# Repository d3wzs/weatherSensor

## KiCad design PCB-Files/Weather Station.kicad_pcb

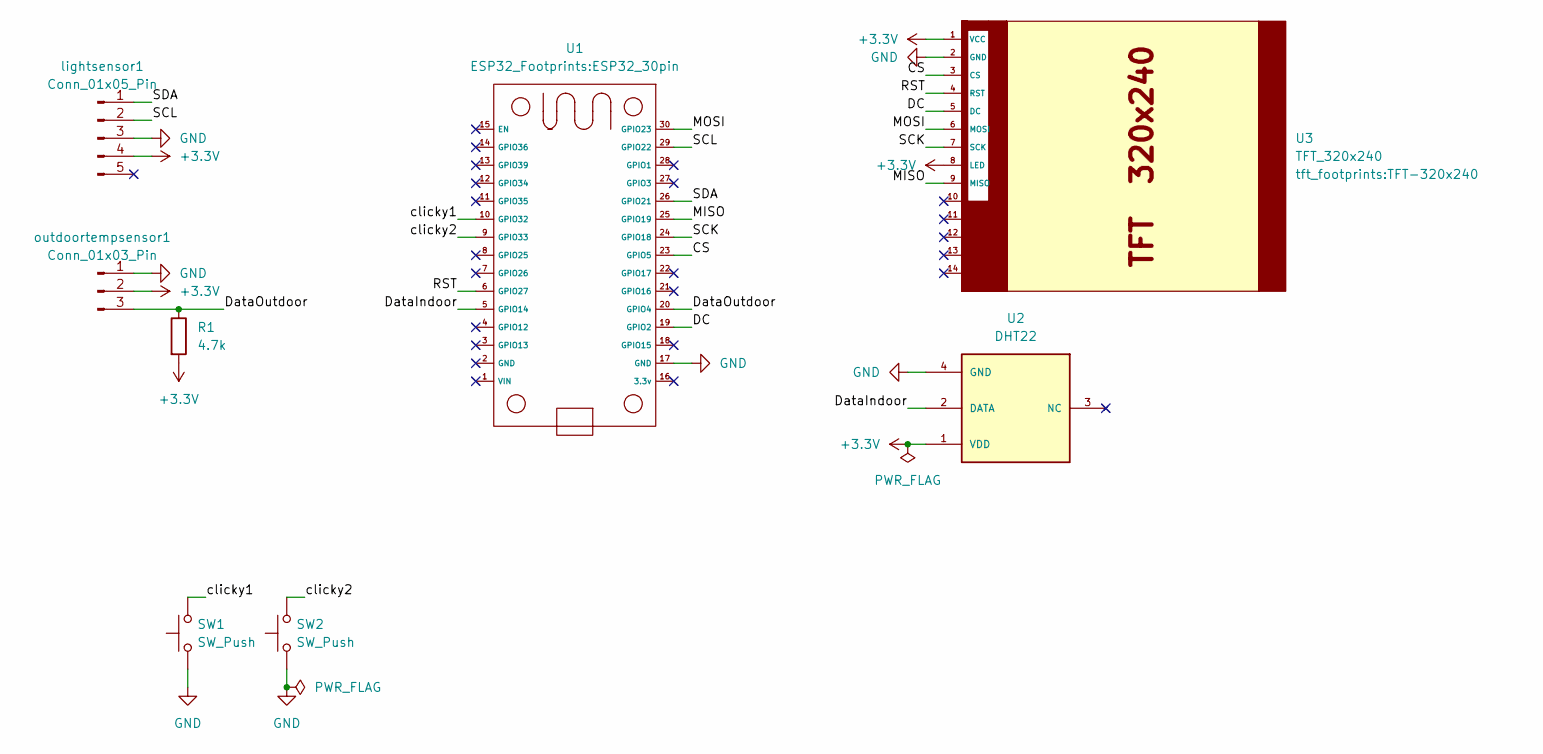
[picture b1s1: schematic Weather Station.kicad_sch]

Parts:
R1: 4.7k; R_Axial_DIN0207_L6.3mm_D2.5mm_P7.62mm_Horizontal
SW1, SW2: SW_Push; Kailh Choc Low-Profile Switches
U1: ESP32_30pin
U2: DHT22; XDCR_DHT22
U3: TFT_320x240; TFT-320x240
lightsensor1: Conn_01x05_Pin; PinHeader_1x05_P2.54mm_Vertical
outdoortempsensor1: Conn_01x03_Pin; FanPinHeader_1x03_P2.54mm_Vertical

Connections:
+3.3V: R1.2, U2.1 (VDD), U3.1 (VCC), U3.8 (LED), lightsensor1.4, outdoortempsensor1.2
/CS: U1.23 (GPIO5), U3.3 (CS)
/DC: U1.19 (GPIO2), U3.5 (DC)
/DataIndoor: U1.5 (GPIO14), U2.2 (DATA)
/DataOutdoor: R1.1, U1.20 (GPIO4), outdoortempsensor1.3
/MISO: U1.25 (GPIO19), U3.9 (MISO)
/MOSI: U1.30 (GPIO23), U3.6 (MOSI)
/RST: U1.6 (GPIO27), U3.4 (RST)
/SCK: U1.24 (GPIO18), U3.7 (SCK)
/SCL: U1.29 (GPIO22), lightsensor1.2
/SDA: U1.26 (GPIO21), lightsensor1.1
/clicky1: SW1.2, U1.10 (GPIO32)
/clicky2: SW2.2, U1.9 (GPIO33)
GND: SW1.1, SW2.1, U1.17 (GND), U2.4 (GND), U3.2 (GND), lightsensor1.3, outdoortempsensor1.1

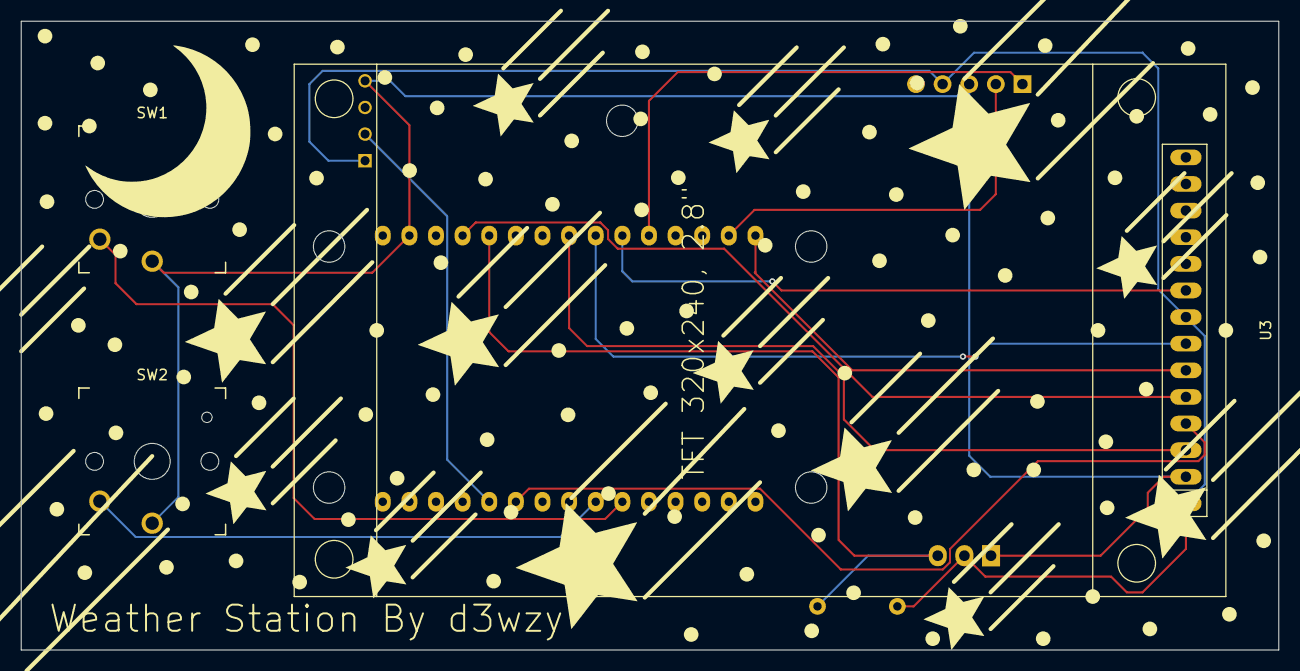
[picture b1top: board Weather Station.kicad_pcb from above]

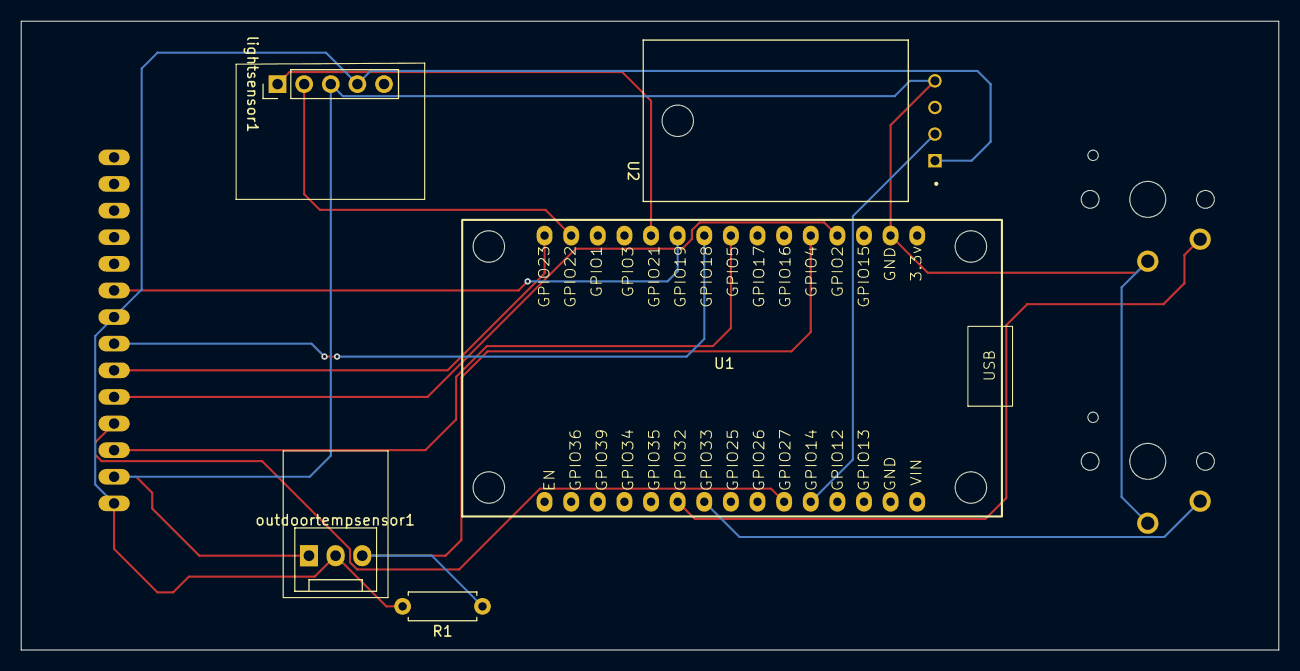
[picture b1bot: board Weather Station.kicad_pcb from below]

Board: 2 copper layers, 120.0 x 60.0 mm, 8 parts (5 on the bottom side), 14 nets.
